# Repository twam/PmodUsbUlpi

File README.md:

Pmod™ Compatible USB ULPI PHY
===

[![CC BY-SA 4.0][cc-by-sa-shield]][cc-by-sa]

This work is licensed under a [Creative Commons Attribution-NonCommercial-ShareAlike 4.0 International License][cc-by-sa].

[![CC BY-SA 4.0][cc-by-sa-image]][cc-by-sa]

[cc-by-sa]: http://creativecommons.org/licenses/by-nc-sa/4.0/
[cc-by-sa-image]: https://licensebuttons.net/l/by-nc-sa/4.0/88x31.png
[cc-by-sa-shield]: https://img.shields.io/badge/License-CC%20BY--NC--SA%204.0-lightgrey.svg

## Images

### JLCPCB

PCBs can be ordered fully-assembled (besides the pin header) from [JLCPCB](https://jlcpcb.com). Required files are
[PmodUsbUlpi_cpl_jlc.csv](PmodUsbUlpi_cpl_jlc.csv), [PmodUsbUlpi_bom_jlc.csv](PmodUsbUlpi_cpl_jlc.csv) and
[Gerber/PmodUsbUlpi.zip](Gerber/PmodUsbUlpi.zip).

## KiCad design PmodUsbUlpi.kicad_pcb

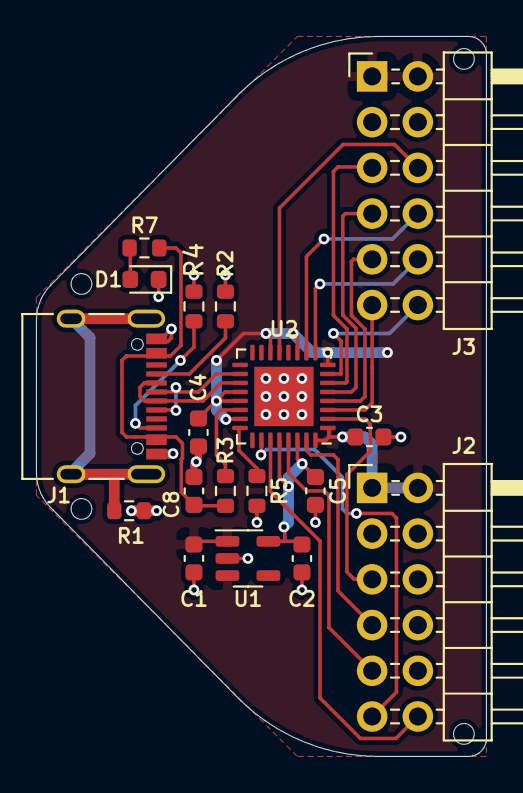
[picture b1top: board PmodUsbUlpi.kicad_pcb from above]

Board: 2 copper layers, 25.0 x 40.0 mm, 18 parts (0 on the bottom side), 25 nets.

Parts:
C1: 1u; C_0603_1608Metric
C2: 10u; C_0603_1608Metric
C3, C5: 100n; C_0603_1608Metric
C4, C8: 2u2; C_0603_1608Metric
D1: green; LED_0603_1608Metric
J1: USB_C_Receptacle_USB2.0; USB_C_Receptacle_XKB_U262-16XN-4BVC11
J2: PMOD1; PinHeader_2x06_P2.54mm_Horizontal
J3: PMOD2; PinHeader_2x06_P2.54mm_Horizontal
R1: 1M; R_0603_1608Metric
R2, R4: 5k1; R_0603_1608Metric
R3: 10k; R_0603_1608Metric
R5: 8k06 1%; R_0603_1608Metric
R7: 15k; R_0603_1608Metric
U1: TPS76318; SOT-23-5
U2: USB3320; QFN-32-1EP_5x5mm_P0.5mm_EP3.3x3.3mm

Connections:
+1V8: C2.1, C5.1, U1.5, U2.28, U2.30
+3V3: C1.1, C3.1, C4.1, J2.1, J2.2, J3.1, J3.2, U1.1, U1.3, U2.1, U2.8, U2.11, U2.14, U2.20, U2.21, U2.23, U2.32
/CC1: J1.A5, R2.1
/CC2: J1.B5, R4.2
/CLK: J2.11, U2.26
/D+: J1.A6, J1.B6, U2.18
/D-: J1.A7, J1.B7, U2.19
/DATA0: J3.11, U2.3
/DATA1: J3.9, U2.4
/DATA2: J3.7, U2.5
/DATA3: J3.5, U2.6
/DATA4: J3.12, U2.7
/DATA5: J3.10, U2.9
/DATA6: J3.8, U2.10
/DATA7: J3.6, U2.13
/DIR: J2.7, U2.31
/NXT: J2.5, U2.2
/RESET: J2.12, U2.27
/STP: J2.9, U2.29
GND: C1.2, C2.2, C3.2, C4.2, C5.2, C8.2, D1.1, J1.A1, J1.A12, J1.B1, J1.B12, J2.3, J2.4, J3.3, J3.4, R1.1, R2.2, R4.1, R5.2, U1.2, U2.33
unnamed: D1.2, R7.2
unnamed: J1.S1, R1.2
unnamed: R3.2, U2.22
unnamed: R5.1, U2.24
VBUS: C8.1, J1.A4, J1.A9, J1.B4, J1.B9, R3.1, R7.1

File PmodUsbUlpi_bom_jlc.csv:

"Comment","Designator","Footprint","LCSC Part #"
"1u","C1","C_0603_1608Metric","C15849"
"10u","C2","C_0603_1608Metric","C19702"
"100n","C5,C3","C_0603_1608Metric","C14663"
"2u2","C8,C4","C_0603_1608Metric","C23630"
"green","D1","LED_0603_1608Metric","C72043"
"USB_C_Receptacle_USB2.0","J1","USB_C_Receptacle_XKB_U262-16XN-4BVC11","C165948"
"1M","R1","R_0603_1608Metric","C22935"
"10k","R3","R_0603_1608Metric","C25804"
"5k1","R4,R2","R_0603_1608Metric","C23186"
"8k06 1%","R5","R_0603_1608Metric","C23112"
"15k","R7","R_0603_1608Metric","C22809"
"TPS76318","U1","SOT-23-5","C7099"
"USB3320","U2","QFN-32-1EP_5x5mm_P0.5mm_EP3.3x3.3mm","C132156"

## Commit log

2021-02-28 Initial commit. Rev 2.
2021-02-28 Add schematic PDF for Rev. 2
2021-03-13 Add README
2021-04-01 Add JLCPCB info to Readme
2022-04-30 Create Dadan2
    Notify me

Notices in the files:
PmodUsbUlpi.kicad_pcb:
License: CC-BY-SA 4.0
